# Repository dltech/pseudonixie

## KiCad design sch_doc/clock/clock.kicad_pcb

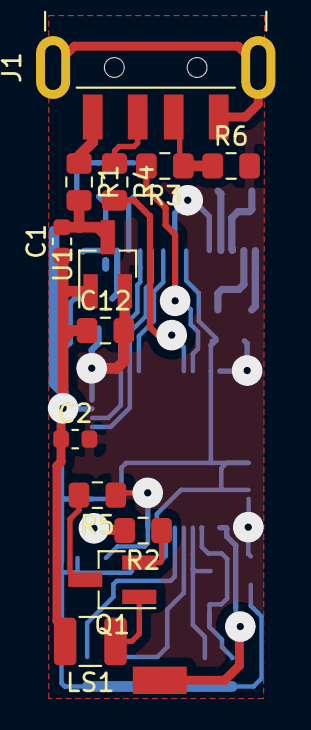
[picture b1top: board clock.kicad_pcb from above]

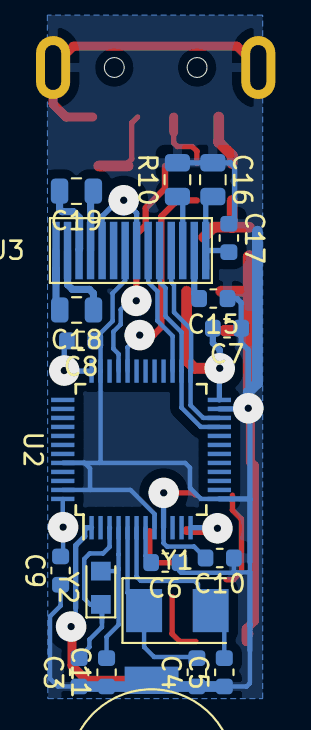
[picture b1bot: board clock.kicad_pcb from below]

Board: 2 copper layers, 33 parts (20 on the bottom side), 28 nets.

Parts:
BT1: Battery_Cell; CR927
C1, C2, C6, C7, C8, C9, C10, C15, C17: 0.1uF; C_0603_1608Metric
C3, C4, C5, C11: 10pF; C_0603_1608Metric
C12: 1uF; C_0805_2012Metric_Pad1.15x1.40mm_HandSolder
C16: 4.7uF; C_0805_2012Metric
C18, C19: 1uF; C_0805_2012Metric
J1: USB_A; USB_A_CNCTech_1001-011-01101_Horizontal
J3: Display; display_14p
LS1: Speaker; C_1210_3225Metric
Q1: AO3400; SOT-23_Handsoldering
R1: 10; R_0805_2012Metric_Pad1.15x1.40mm_HandSolder
R2, R6: 1k; R_0805_2012Metric_Pad1.15x1.40mm_HandSolder
R3, R4: 22; R_0805_2012Metric_Pad1.15x1.40mm_HandSolder
R5: 120; R_0805_2012Metric_Pad1.15x1.40mm_HandSolder
R10: 560k; R_0805_2012Metric
U1: XC6206-33; SOT-23_Handsoldering
U2: STM32F103C8TxSmall; TQFP-48_7x7mm_P0.5mm
Y1: 8MHz; Crystal_SMD_5032-2Pin_5.0x3.2mm
Y2: 32768; Crystal_SMD_2012-2Pin_2.0x1.2mm_HandSoldering

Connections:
+3V3: C2.2, C7.2, C8.2, C9.2, C10.2, C12.2, J3.5, J3.8, R5.1, R6.2, U1.2, U2.9, U2.24, U2.36, U2.48
/DM: R4.2, U2.32
/DP: R3.2, U2.33
/D_RST: J3.9, U2.27
/D_SCL: J3.10, U2.21, U2.26
/D_SDA: J3.11, U2.22, U2.25
/SP: R2.2, U2.12
GND: BT1.2, C1.1, C2.1, C3.1, C4.1, C5.1, C6.1, C7.1, C8.1, C9.1, C10.1, C11.1, C12.1, C15.1, C16.1, C17.1, J1.4, J1.5, J3.7, LS1.2, R10.2, U1.1, U2.8, U2.13, U2.23, U2.35, U2.44, U2.47
unnamed: BT1.1, U2.1
unnamed: C1.2, R1.2, U1.3
unnamed: C3.2, U2.3, Y2.1
unnamed: C4.2, U2.5, Y1.1
unnamed: C5.2, U2.6, Y1.2
unnamed: C6.2, U2.7
unnamed: C11.2, U2.4, Y2.2
unnamed: C15.2, J3.13
unnamed: C16.2, C17.2, J3.14
unnamed: C18.1, J3.2
unnamed: C18.2, J3.1
unnamed: C19.1, J3.4
unnamed: C19.2, J3.3
unnamed: J1.2, R4.1
unnamed: J1.3, R3.1, R6.1
unnamed: J3.12, R10.1
unnamed: LS1.1, Q1.1
unnamed: Q1.2, R2.1
unnamed: Q1.3, R5.2
VBUS: J1.1, R1.1

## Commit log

2020-06-16 первый коммит
2020-08-01 плата готова
